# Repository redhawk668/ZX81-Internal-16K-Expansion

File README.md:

# ZX81-Internal-16K-Expansion 'No Wobbly Edition'
This little PCB is a 'quick and dirty, no wobbly' 16K internal memory expansion for the Sinclair ZX81. The ZX81 is a very simple computer and only has 1KB of memory, which could be expanded to 16KB by using a RAMpack. This had to be connected to the expansion port on the back of the computer. It is this RAMpack that was notorious for the infamous 'RAMpack wobble', a certain movement of the computer would cause a crash, resulting in losing work, etc. 

That is where the 'No Wobbly Edition' comes in, it replaces the internal 1KB SRAM with a 32KB SRAM, of which 16KB is usable. All of the necessary re-routing of address lines is done on the PCB, there is no need to cut tracks on the ZX81 PCB or bending of pins, etc. It is easily reversible by inserting a 6116 SRAM in the socket.

This expansion also has a 10K resistor between pin 28 (+5 volt) and pin 27 (WE) for HRG8 (High Res) compatibility.

# The PCB (Rev. A):

# Billing of Materials:
|Qty  |Value  |Component            |Package  |PCB  |
|-----|-------|---------------------|---------|-----|
| 1x  | 10K   | Resistor            | 1206    | R1  |
| 1x  | 0.1uF | Ceramic Capacitor   | 1206    | C1  |
| 1x  |       | 62256 32Kx8 SRAM    | SOP-28  | U1  |
|     |       | Pin Socket Strip    |         |     |
-----------------------------------------------------

# Installation:
First desolder the old RAM chips. Clear out the holes and solder a 28 pin socket on the ZX81 PCB. There is jumper link on the ZX81 PCB, this has to be set to LK2 (L2 on Issue 1 PCB's). This routes address line A10 to the corresponding pin on the memory expansion. Solder wires to the address lines A11, A12 & A13 on the memory expansion PCB. 
- Solder the other end of the A11 wire to the cathode of D1
- Solder the other end of the A12 wire to the cathode of D3
- Solder the other end of the A13 wire to the cathode of D5

Insert the memory expansion into the socket.

It should look like this (installed on Issue 3 PCB):

Re-assemble the ZX81 and turn it on, it should take a few seconds before the 'K' appears.

To test the memory expansion, run the following command:

PRINT PEEK 16388+256*PEEK 16389

Result should be 32768.

# ZX81 - Internal-32K-Expansion 'vLA81 Edition'
Rev. B of the memory expansion. The vLA81 is an awesome replacement for the ZX81 ULA. It has all the needed logic in it's CPLD to do all the decoding to give the ZX81 the full 32KB. It is very similar to the 16KB expansion, it only needs an extra Address Line (A14) to make the magic happen. 

# The PCB (Rev. B):

# Billing of Materials:
Same as Rev. A

# Installation:
Same as the 16KB expansion. It only needs one more Address Line connected.

Address Line A14 must be soldered to the cathode of D7, the rest is the same as Rev. A.

Connect pin 3 of the Z80 (A13) to pin 35 of the vLA81. Normally this is reserved for the clock signal from the resonator. The vLA81 has it's own clock crystal, so this pin has another purpose.

# Memory configurations:
- Both dipswitches USR0/USR1 to off: 16KB
- Dipswitch USR0 to on and USR1 to off: 16 - 48KB, suitable for hires programs
- Dipswitch USR0 to off and USR1 to on: 8K - 40K, provides lower 32K memory map for WRX hires programs
- Both dipswitches to on, provides soft config.

To activate the full 32KB, the ZX81 has to be told to raise it's RAMTOP, normally it will only see the first 16KB.

Run the following commands:

POKE 16389,255 followed by a NEW command. This will raise the RAMTOP and the ZX81 will now be able to use the full 32KB.

Depending on the dipswitches, the command:

PRINT PEEK 16388+256*PEEK 16389

Will result in 49152 or 40960.

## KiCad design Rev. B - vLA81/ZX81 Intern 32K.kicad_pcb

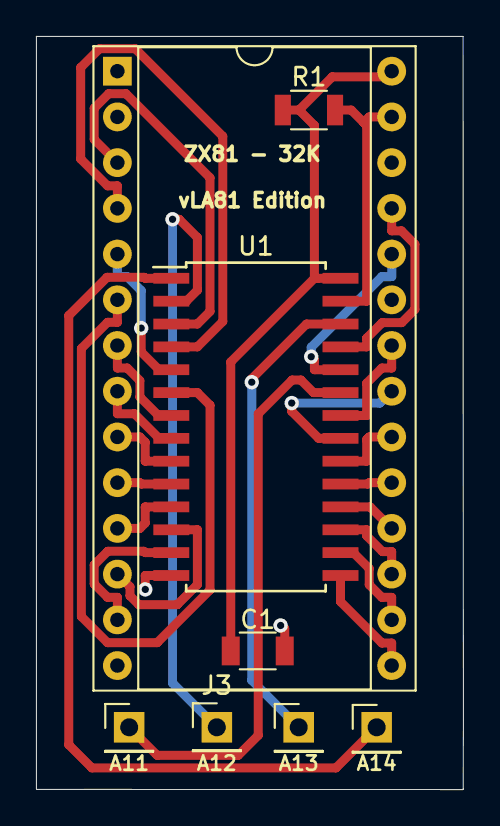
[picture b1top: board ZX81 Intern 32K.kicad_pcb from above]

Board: 2 copper layers, 23.7 x 41.8 mm, 7 parts (0 on the bottom side), 7 nets.

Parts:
C1: 0.1uF; C_1206
J1: A14; Pin_Header_Straight_1x01_Pitch2.54mm
J2: A13; Pin_Header_Straight_1x01_Pitch2.54mm
J3: A12; Pin_Header_Straight_1x01_Pitch2.54mm
J4: A11; Pin_Header_Straight_1x01_Pitch2.54mm
R1: 10K; R_1206
U1: CY62256-70PC; SOIC-28W_7.5x17.9mm_Pitch1.27mm

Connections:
+5V: C1.1, R1.1, U1.28
GND: C1.2, U1.14
unnamed: J1.1, U1.1
unnamed: J2.1, U1.26
unnamed: J3.1, U1.2
unnamed: J4.1, U1.23
unnamed: R1.2, U1.27

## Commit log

2021-05-11 Create LICENSE
